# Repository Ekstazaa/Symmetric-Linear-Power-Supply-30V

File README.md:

# 🔌 Symetryczny zasilacz liniowy ±30 V

Projekt liniowego zasilacza symetrycznego przeznaczonego do zastosowań laboratoryjnych oraz testowania układów analogowych.

Układ umożliwia regulację napięcia dodatniego i ujemnego względem wspólnej masy oraz został zaprojektowany i zbudowany od podstaw – od schematu, przez PCB, aż po kompletną obudowę.

---

## 📷 Zdjęcia

### 🔧 Wnętrze

### 🎛️ Panel przedni

### 🔌 Tył

---

## ⚙️ Specyfikacja
\
| Parametr | Wartość |
|--------|--------|
| Napięcie wyjściowe | ±1.5 V do ±24 V (testowane) |
| Maksymalny prąd z jednej linii | ~1.5 A (regulatory) / ~4.5 A (z tranzystorami) |
| Transformator | toroidalny |
| Prąd transformatora | ~1.25 A |
| Topologia | liniowa |

---

## 🧠 Architektura

### Główne elementy:
- transformator toroidalny  
- mostek prostowniczy  
- kondensatory filtrujące  
- regulatory LM317 / LM337  
- tranzystory mocy (zwiększenie wydajności prądowej)  

---

## 🔌 Wyjścia

- 🔴 czerwony — +V  
- 🟢 zielony — GND  
- ⚫ czarny — -V  

---

## 🧪 Testy

Zasilacz został przetestowany przy użyciu prostych obciążeń (LED + rezystor).

Obserwacje:
- poprawna regulacja napięcia w całym zakresie  
- stabilna praca  
- brak zauważalnych problemów z regulacją  

---

## ⚠️ Problemy i kompromisy projektowe

### Inrush current

Największym problemem projektu okazał się prąd rozruchowy.

Duże kondensatory filtrujące na wejściu powodują:
- bardzo duży impuls prądu przy starcie  
- przepalanie bezpiecznika 1 A w gnieździe zasilania  

Tymczasowe rozwiązanie:
- zastosowanie bezpiecznika 4.5 A  

Nie jest to rozwiązanie docelowe, ponieważ:
- przekracza nominalny prąd transformatora (~1.25 A)  
- zmniejsza skuteczność zabezpieczenia  

Planowane rozwiązania:
- przeniesienie kondensatorów redukujących tętnienia z przed regulatorami do wyjścia regulatorów, które mają już konstrukcje softstartu.

---

### Ograniczenie prądu

- regulatory LM317 / LM337 posiadają ograniczenie prądowe (~1.5 A)  
- tranzystory mocy nie są zabezpieczone  

Planowane ulepszenie:
- zworka / bezpiecznik w torze tranzystorów  
- łatwiejsze debugowanie i zabezpieczenie układu  

### Kondensatory X i Y

- brakuje kondensatorów bezpieczeństaw X i Y

---

### Pomiar napięcia

Zastosowane analogowe mierniki:
- nie rozróżniają napięcia ujemnego  
- wskazują wartość bez uwzględnienia znaku  

---

### Mechanika i chłodzenie

- obudowa jest dość ciasna  
- ograniczony przepływ powietrza  
- potencjalne problemy termiczne przy dużym obciążeniu  

---

## 💬 Podsumowanie

Projekt jest w pełni działający i spełnia swoje założenia, jednak wymaga dalszego dopracowania w zakresie:

- zarządzania prądem rozruchowym  
- zabezpieczeń  
- warunków termicznych

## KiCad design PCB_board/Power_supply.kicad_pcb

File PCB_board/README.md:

# Regulowany symetryczny zasilacz liniowy (Dual-Rail)

https://github.com/Ekstazaa/Symmetric-Linear-Power-Supply-30V/blob/main/PCB_board/README.md

---

## 📖 Opis

Ta płytka PCB implementuje transformatorowy, regulowany, symetryczny zasilacz liniowy oparty na układach LM317 (szyna dodatnia) oraz LM337 (szyna ujemna).  

Projekt jest przeznaczony do zastosowań laboratoryjnych oraz audio, gdzie wymagane jest regulowane napięcie symetryczne.

Zasilacz zawiera tranzystory mocy zwiększające wydajność prądową, zabezpieczenia wyjścia, dodatkową gałąź zasilania dla elektroniki panelowej oraz standardowe elementy stabilizujące zgodne z notami katalogowymi regulatorów.

---

### 🧊 Model 3D:

### 📐 Schemat:

---

## ⚡ Stopień wejściowy

Zasilacz jest zasilany z transformatora o parametrach:

- 2 × 32 VAC  
- Maksymalny prąd: 5 A na uzwojenie  

Prostowanie realizowane jest w konfiguracji dwudiodowej (pełnookresowej).

Po prostowaniu:

Każda szyna zawiera dwa kondensatory filtrujące 4700 µF (łącznie 9.4 mF na szynę).  
Ze względu na umiarkowaną pojemność filtrującą oraz możliwość pracy przy większych obciążeniach, tętnienia napięcia rosną przy wysokim poborze prądu.

---

## 🔧 Stopień regulacji

Regulacja napięcia realizowana jest przy użyciu:

- LM317 (szyna dodatnia)  
- LM337 (szyna ujemna)  

Regulatory są sterowane za pomocą zewnętrznych potencjometrów wieloobrotowych (montowanych na panelu przednim).

Dodatkowo na PCB przewidziano footprinty THT dla potencjometrów, co pozwala:
- używać regulacji bezpośrednio na płytce  
- skonfigurować układ jako źródło napięcia stałego  

Każdy regulator zawiera:

- kondensator wejściowy 100 nF  
- kondensator wyjściowy 1 µF  
- diody zabezpieczające przed rozładowaniem wstecznym  
- układ biasu startowego (kontrola zachowania przy starcie)

---

## 🔋 Stopień zwiększenia prądu

Aby zwiększyć wydajność prądową ponad ograniczenie ~1.5 A regulatorów LM317/LM337, zastosowano po jednym tranzystorze mocy (serii TIP) na każdą szynę.

Pozwala to na uzyskanie większego prądu wyjściowego, przy zachowaniu stabilizacji przez regulatory.

Zabezpieczenia wyjścia:

- bezpiecznik 4 A na każdą szynę  

Projekt zakłada maksymalny prąd ciągły na poziomie około 4 A.

---

## 📈 Maksymalne napięcie wyjściowe

Mimo zastosowania transformatora 2 × 30 VAC, maksymalne stabilizowane napięcie wyjściowe wynosi około:

±28 V DC  

Ograniczenie wynika ze spadków napięcia na:

- diodach prostownika  
- rezystancjach pasożytniczych  
- napięciu dropout regulatorów  
- spadku V_BE tranzystorów TIP  

---

## 🌡️ Warunki termiczne

Ze względu na wysokie napięcie wejściowe, przy niskim napięciu wyjściowym wydzielana jest znaczna moc strat.

Przybliżenie:

P ≈ (Vin - Vout) × Iout  

Ciepło wydziela się głównie w:

- regulatorach LM317 / LM337  
- tranzystorach mocy  

Zastosowane radiatory pozwalają na:

- LM317 / LM337: ~10 W  
- tranzystory TIP: ~17 W  

Zakłada to odpowiedni przepływ powietrza i poprawny montaż mechaniczny.  
Przy dużym prądzie i niskim napięciu wyjściowym może być wymagane dodatkowe chłodzenie.

---

## 🔌 Zasilanie pomocnicze

Dodatkowa gałąź oparta o LM7818 zapewnia:

- zasilanie mierników panelowych  
- diodę sygnalizacyjną LED  

---

## ⚠️ Uwagi projektowe i ograniczenia

Projekt został wykonany z użyciem transformatora 2 × 30 V, głównie ze względu na jego dostępność.  

W praktyce bardziej optymalny byłby transformator o niższym napięciu wtórnym (np. 2 × 16–18 V).

W obecnym zastosowaniu wymagane napięcie to maksymalnie ±12 V, co oznacza, że:

- transformator jest przewymiarowany napięciowo  
- występują duże spadki napięcia na regulatorach  
- generowane są znaczne straty mocy  

W przyszłości planowana jest zmiana transformatora na lepiej dopasowany do zastosowania.  
Obecnie testy wykonywane są bez dużych obciążeń.

Dodatkowo:

- PCB umożliwia montaż potencjometrów THT  
- dostępne są dwa terminale śrubowe na każdą szynę (większa wygoda i elastyczność)

---

## 📁 Opis plików projektu

- **Power_supply.kicad_sch**  
  Schemat elektryczny w KiCad

- **Power_supply.kicad_pcb**  
  Layout PCB (rozmieszczenie elementów i ścieżki)

- **Power_supply.kicad_pro**  
  Plik projektu KiCad

- **Power_supply.zip**  
  Pliki produkcyjne (Gerbery + wiercenia)

- **bom.csv**  
  Lista elementów (Bill of Materials)

- **positions.csv**  
  Plik pick-and-place (pozycje komponentów)

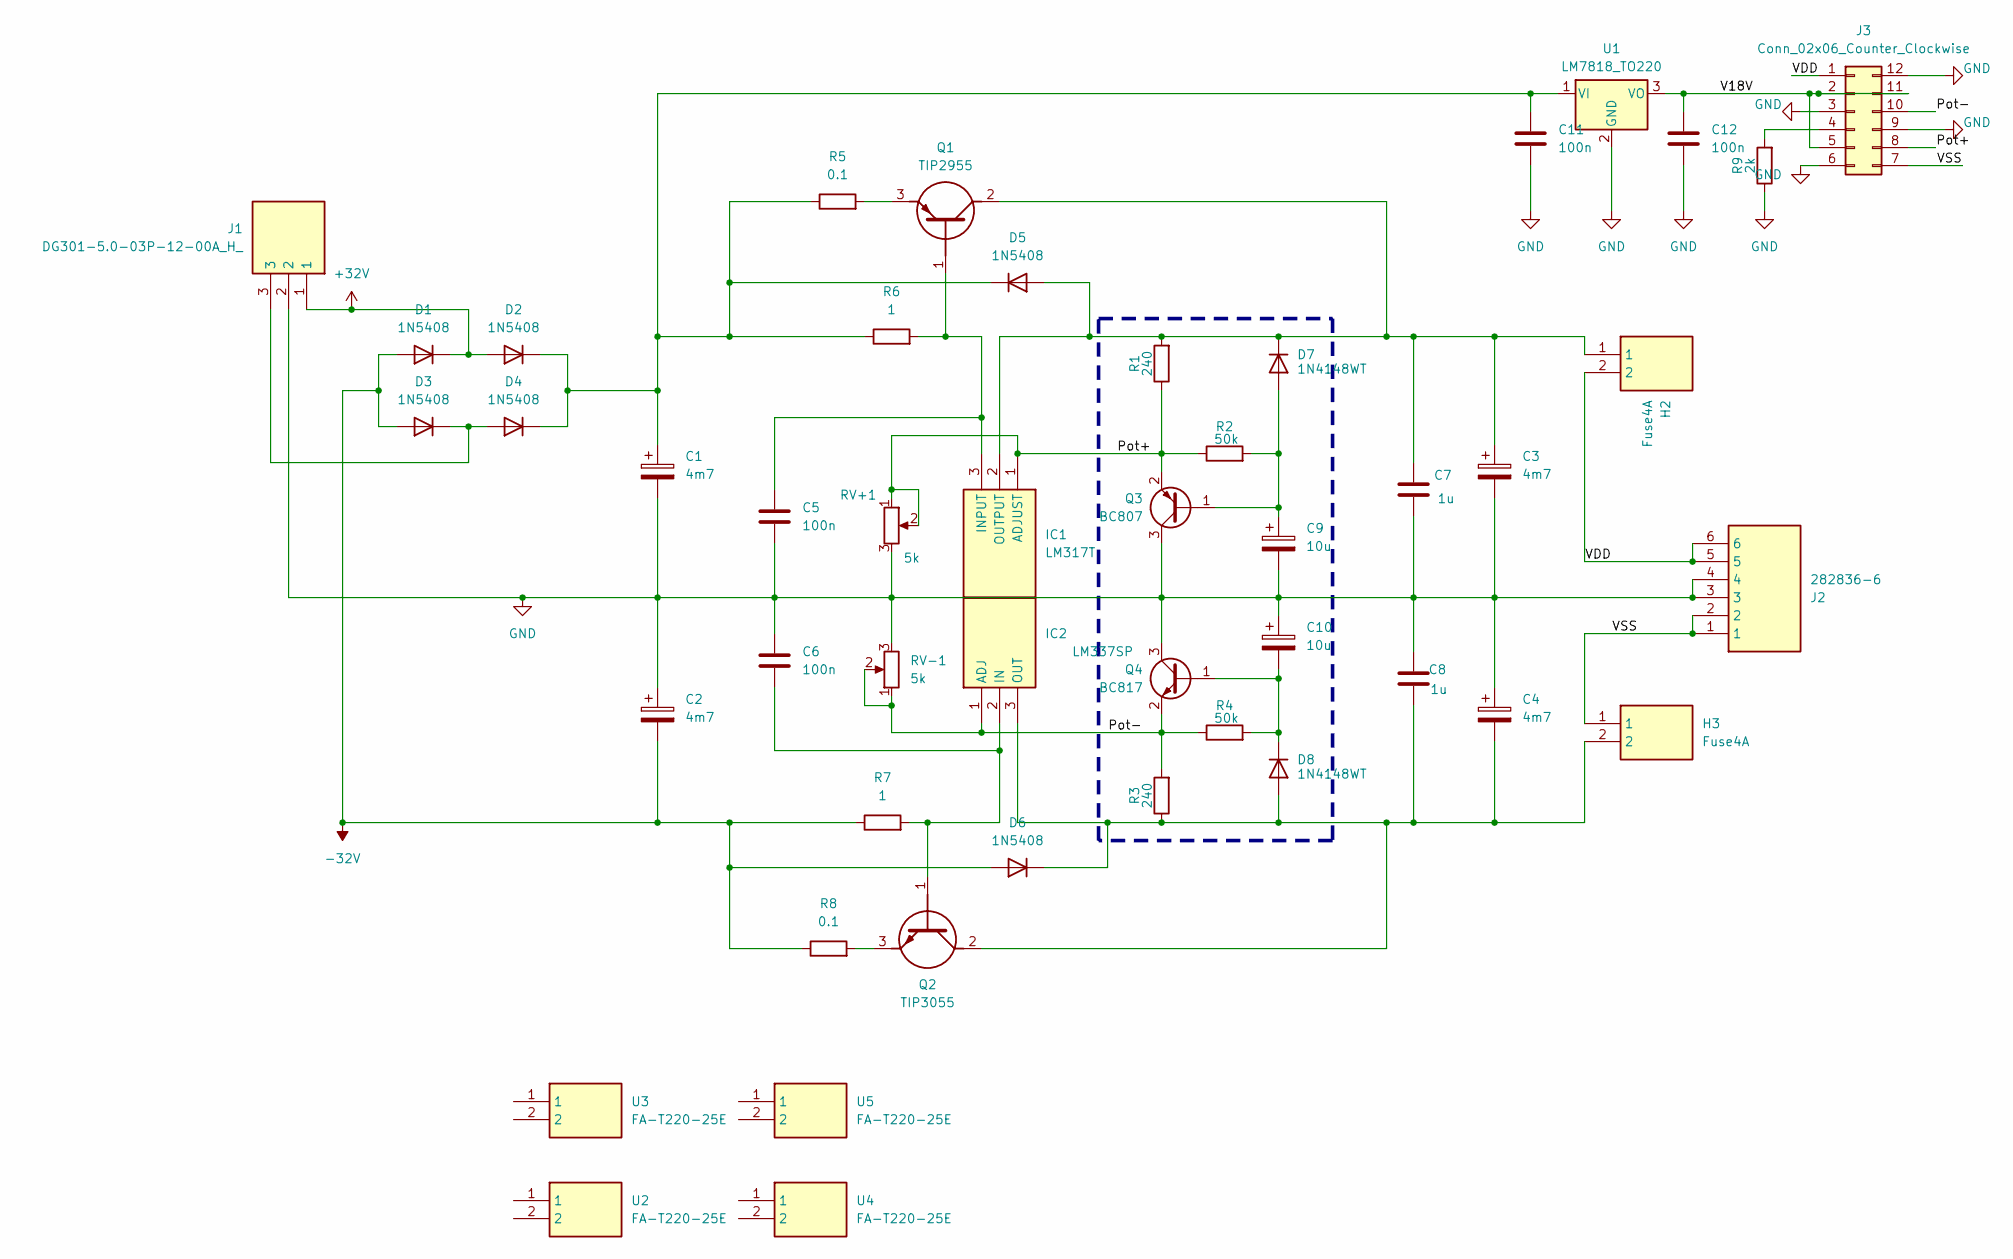
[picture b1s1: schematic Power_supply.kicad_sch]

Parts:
C1, C2, C3, C4: 4m7; HE1J478M30040HA
C5, C6, C11, C12: 100n; C_0805_2012Metric
C7, C8: 1u; C_0805_2012Metric
C9, C10: 10u; C_Radial_D5.0mm_H7.0mm_P2.00mm
D1, D2, D3, D4, D5, D6: 1N5408; D_DO-201AD_P15.24mm_Horizontal
D7, D8: 1N4148WT; D_SOD-523
H2, H3: Fuse4A; PTF15; Manufacturer_Part_Number PTF/15
IC1: LM317T; TO255P460X1020X2008-3P; Manufacturer_Part_Number LM317T
IC2: LM337SP; TO255P460X1020X2008-3P; Manufacturer_Part_Number LM337SP
J1: DG301-5.0-03P-12-00A_H_; DG3015003P1200AH; Manufacturer_Part_Number DG301-5.0-03P-12-00A(H)
J2: 282836-6; 2828366; Manufacturer_Part_Number 282836-6
J3: Conn_02x06_Counter_Clockwise; PinSocket_2x06_P2.54mm_Vertical
Q1: TIP2955; TO545P515X1560X2445-3P; Manufacturer_Part_Number TIP2955
Q2: TIP3055; TO545P515X1560X2445-3P; Manufacturer_Part_Number TIP3055
Q3: BC807; SOT-23
Q4: BC817; SOT-23
R1, R3: 240; R_0603_1608Metric_Pad0.98x0.95mm_HandSolder
R2, R4: 50k; R_0603_1608Metric_Pad0.98x0.95mm_HandSolder
R5, R8: 0.1; R_Axial_DIN0516_L15.5mm_D5.0mm_P20.32mm_Horizontal
R6, R7: 1; R_Axial_DIN0516_L15.5mm_D5.0mm_P20.32mm_Horizontal
R9: 2k; R_0603_1608Metric_Pad0.98x0.95mm_HandSolder
RV+1: 5k; Potentiometer_ACP_CA9-H5_Horizontal
RV-1: 5k; Potentiometer_ACP_CA9-H5_Horizontal
U1: LM7818_TO220; TO-220-3_Vertical
U2, U3, U4, U5: FA-T220-25E; FAT22025E; Manufacturer_Part_Number FA-T220-25E

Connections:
+32V: D1.1 (K), D2.2 (A), J1.1
-32V: C2.2, D1.2 (A), D3.2 (A), D6.2 (A), R7.1, R8.1
/Pot+: IC1.1 (ADJUST), J3.8, Q3.2 (E), R1.1, R2.1, RV+1.1, RV+1.2
/Pot-: IC2.1 (ADJ), J3.10, Q4.2 (E), R3.2, R4.1, RV-1.1, RV-1.2
/V18V: C12.1, J3.2, J3.5, J3.11, U1.3 (VO)
/VDD: H2.2, J2.5, J2.6, J3.1
/VSS: H3.1, J2.1, J2.2, J3.7
GND: C1.2, C2.1, C3.2, C4.1, C5.2, C6.1, C7.2, C8.1, C9.2, C10.1, C11.2, C12.2, J1.2, J2.3, J2.4, J3.3, J3.6, J3.9, J3.12, Q3.3 (C), Q4.3 (C), R9.1, RV+1.3, RV-1.3, U1.2 (GND)
unnamed: C1.1, C11.1, D2.1 (K), D4.1 (K), D5.1 (K), R5.1, R6.1, U1.1 (VI)
unnamed: D3.1 (K), D4.2 (A), J1.3
unnamed: C3.1, C7.1, D5.2 (A), D7.1 (K), H2.1, IC1.2 (OUTPUT), Q1.2 (C), R1.2
unnamed: C4.2, C8.2, D6.1 (K), D8.2 (A), H3.2, IC2.3 (OUT), Q2.2 (C), R3.1
unnamed: C9.1, D7.2 (A), Q3.1 (B), R2.2
unnamed: C10.2, D8.1 (K), Q4.1 (B), R4.2
unnamed: C5.1, IC1.3 (INPUT), Q1.1 (B), R6.2
unnamed: C6.2, IC2.2 (IN), Q2.1 (B), R7.2
unnamed: J3.4, R9.2
unnamed: Q1.3 (E), R5.2
unnamed: Q2.3 (E), R8.2

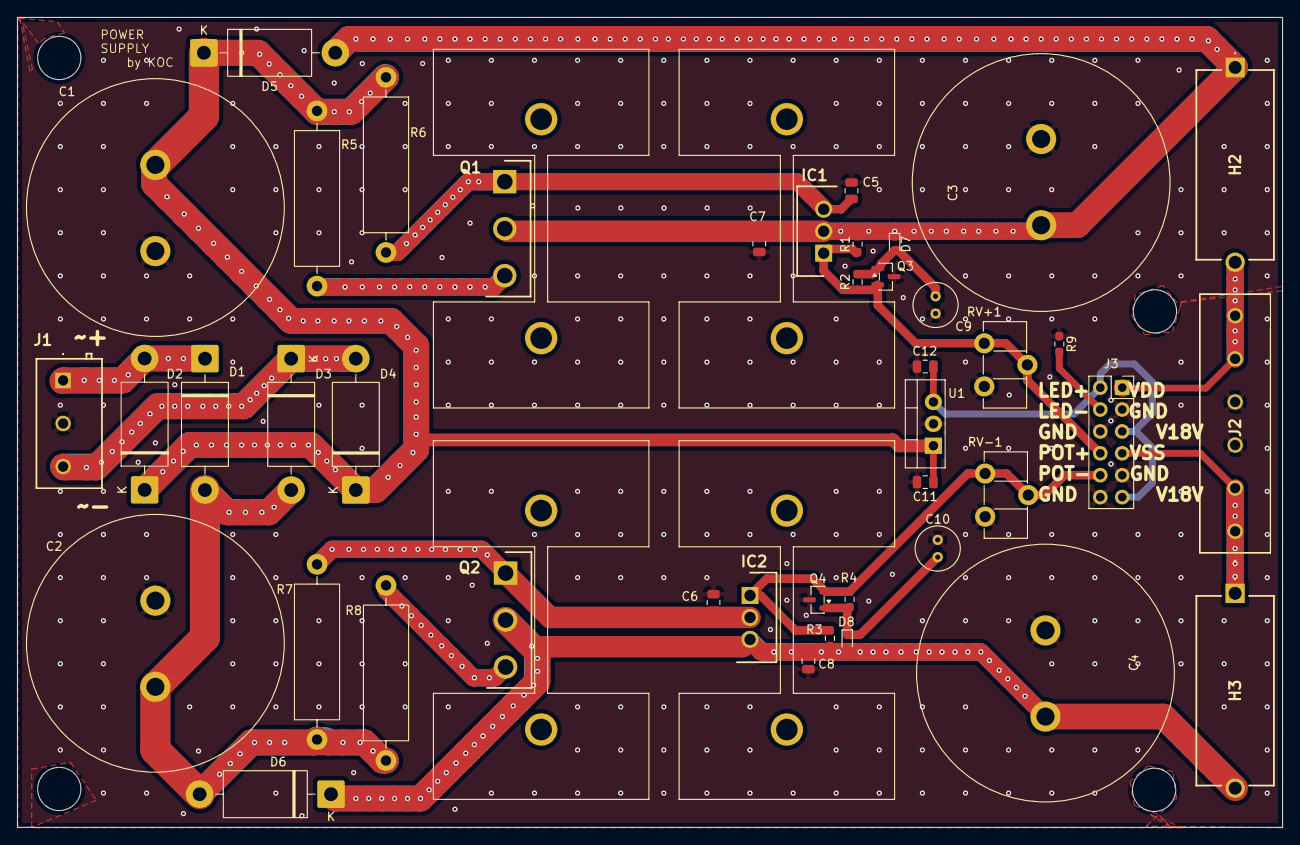
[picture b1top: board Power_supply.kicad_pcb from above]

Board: 2 copper layers, 146.8 x 93.9 mm, 47 parts (0 on the bottom side), 19 nets.

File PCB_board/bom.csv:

Designator,Footprint,Quantity,Value,LCSC Part #
"C1, C2, C3, C4",HE1J478M30040HA,4,4m7,
"C10, C9",C_Radial_D5.0mm_H7.0mm_P2.00mm,2,10u,
"C11, C12, C5, C6",0805,4,100n,
"C7, C8",0805,2,1u,
"D1, D2, D3, D4, D5, D6",D_DO-201AD_P15.24mm_Horizontal,6,1N5408,
"D7, D8",D_SOD-523,2,1N4148WT,
"H2, H3",PTF15,2,Fuse4A,
IC1,TO255P460X1020X2008-3P,1,LM317T,
IC2,TO255P460X1020X2008-3P,1,LM337SP,
J1,DG3015003P1200AH,1,DG301-5.0-03P-12-00A_H_,
J2,2828366,1,282836-6,
J3,PinSocket_2x06_P2.54mm_Vertical,1,Conn_02x06_Counter_Clockwise,
Q1,TO545P515X1560X2445-3P,1,TIP2955,
Q2,TO545P515X1560X2445-3P,1,TIP3055,
Q3,SOT-23,1,BC807,
Q4,SOT-23,1,BC817,
"R1, R3",0603,2,240,
"R2, R4",0603,2,50k,
"R5, R8",R_Axial_DIN0516_L15.5mm_D5.0mm_P20.32mm_Horizontal,2,0.1,
"R6, R7",R_Axial_DIN0516_L15.5mm_D5.0mm_P20.32mm_Horizontal,2,1,
R9,0603,1,2k,
"RV+1, RV-1",Potentiometer_ACP_CA9-H5_Horizontal,2,R_Potentiometer,
U1,TO-220-3_Vertical,1,LM7818_TO220,
"U2, U3, U4, U5",FAT22025E,4,FA-T220-25E,

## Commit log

2026-02-21 Create README.md
    PCB descripe
2026-02-21 Update README.md
    added files explenation
2026-05-02 Update README.md
    zmiana na polski
2026-05-15 Update README.md
    .
